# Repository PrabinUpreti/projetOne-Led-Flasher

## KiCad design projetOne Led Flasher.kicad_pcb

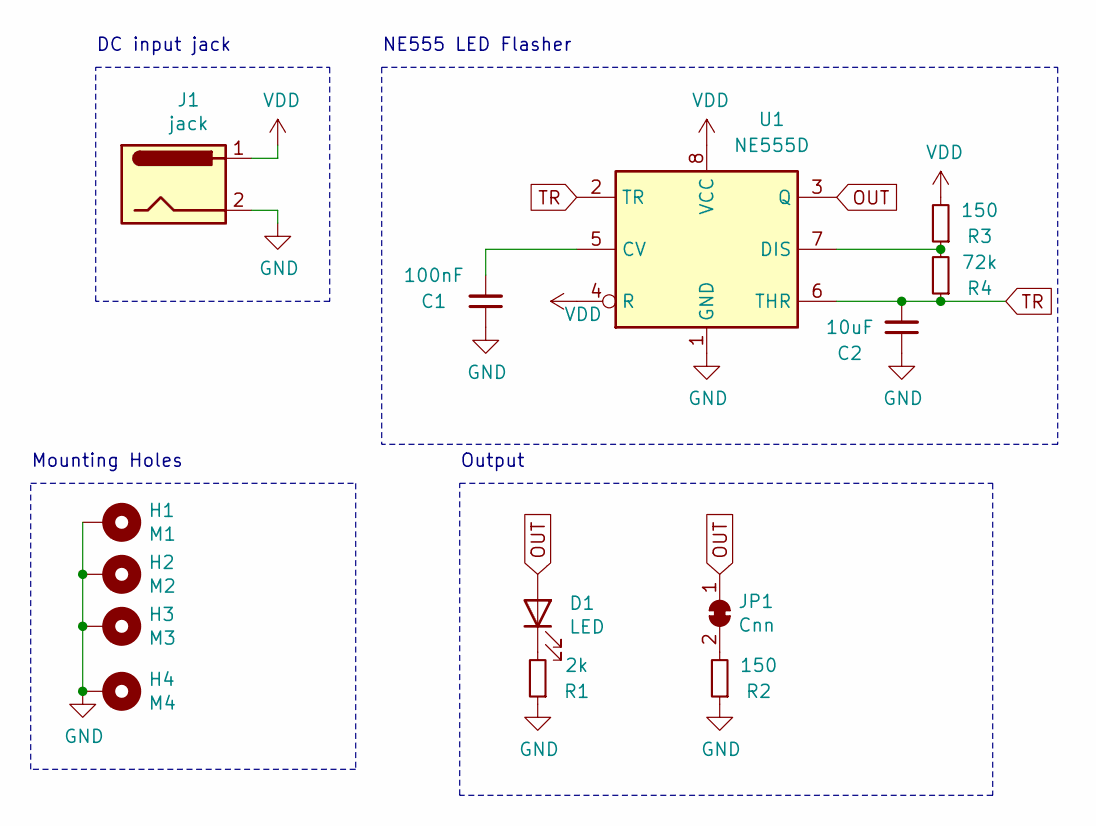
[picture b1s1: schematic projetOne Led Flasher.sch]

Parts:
C1: 100nF; C_Disc_D3.0mm_W1.6mm_P2.50mm
C2: 10uF; CP_Radial_D4.0mm_P1.50mm
D1: LED; LED_D3.0mm
H1: M1; MountingHole_2.2mm_M2_Pad_Via
H2: M2; MountingHole_2.2mm_M2_Pad_Via
H3: M3; MountingHole_2.2mm_M2_Pad_Via
H4: M4; MountingHole_2.2mm_M2_Pad_Via
J1: jack; BarrelJack_Horizontal
JP1: Cnn; SolderJumper-2_P1.3mm_Open_RoundedPad1.0x1.5mm
R1: 2k; R_Axial_DIN0204_L3.6mm_D1.6mm_P5.08mm_Horizontal
R2, R3: 150; R_Axial_DIN0204_L3.6mm_D1.6mm_P5.08mm_Horizontal
R4: 72k; R_Axial_DIN0204_L3.6mm_D1.6mm_P5.08mm_Horizontal
U1: NE555D; DIP-8_W10.16mm_LongPads

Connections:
GND: C1.1, C2.1, H1.1, H2.1, H3.1, H4.1, J1.2, R1.1, R2.1, U1.1 (GND)
unnamed: C1.2, U1.5 (CV)
unnamed: D1.1 (K), R1.2
unnamed: JP1.2 (B), R2.2
unnamed: R3.1, R4.2, U1.7 (DIS)
OUT: D1.2 (A), JP1.1 (A), U1.3 (Q)
TR: C2.2, R4.1, U1.2 (TR), U1.6 (THR)
VDD: J1.1, R3.2, U1.4 (R), U1.8 (VCC)

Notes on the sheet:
DC input jack
NE555 LED Flasher
Output
Mounting Holes

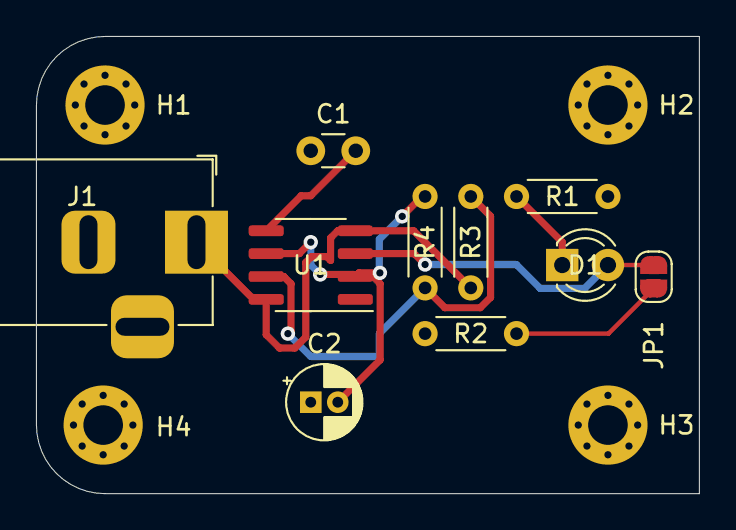
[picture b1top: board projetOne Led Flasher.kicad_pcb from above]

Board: 2 copper layers, 36.8 x 25.4 mm, 14 parts (0 on the bottom side), 8 nets.

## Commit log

2021-05-01 Added Externelal libraries
2021-05-01 Added libraried
